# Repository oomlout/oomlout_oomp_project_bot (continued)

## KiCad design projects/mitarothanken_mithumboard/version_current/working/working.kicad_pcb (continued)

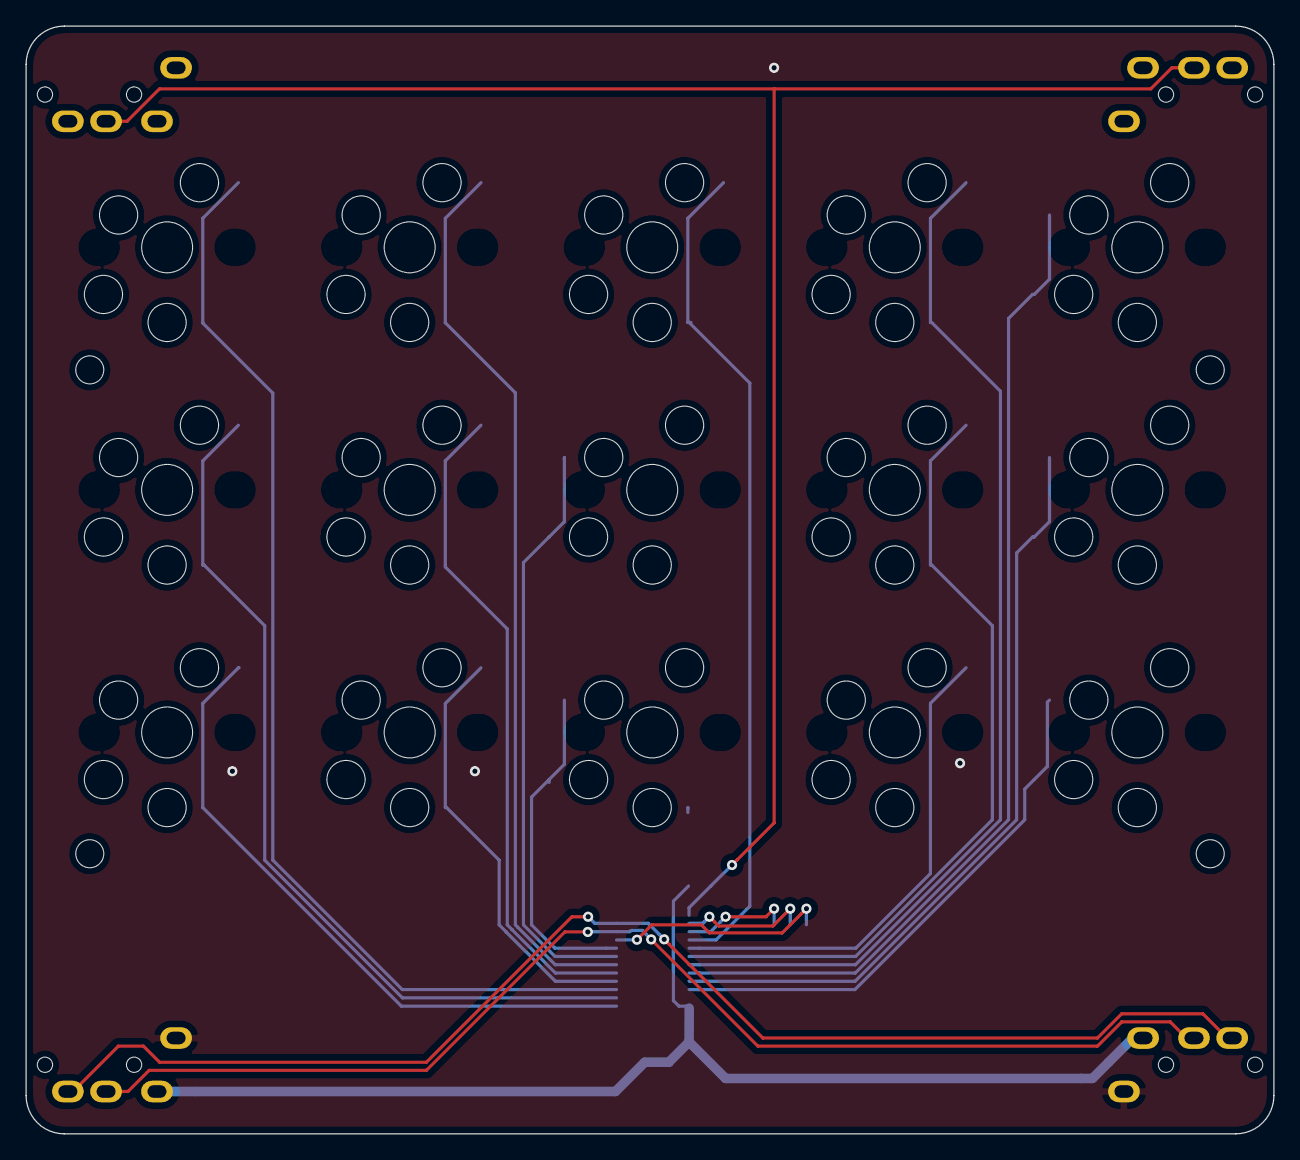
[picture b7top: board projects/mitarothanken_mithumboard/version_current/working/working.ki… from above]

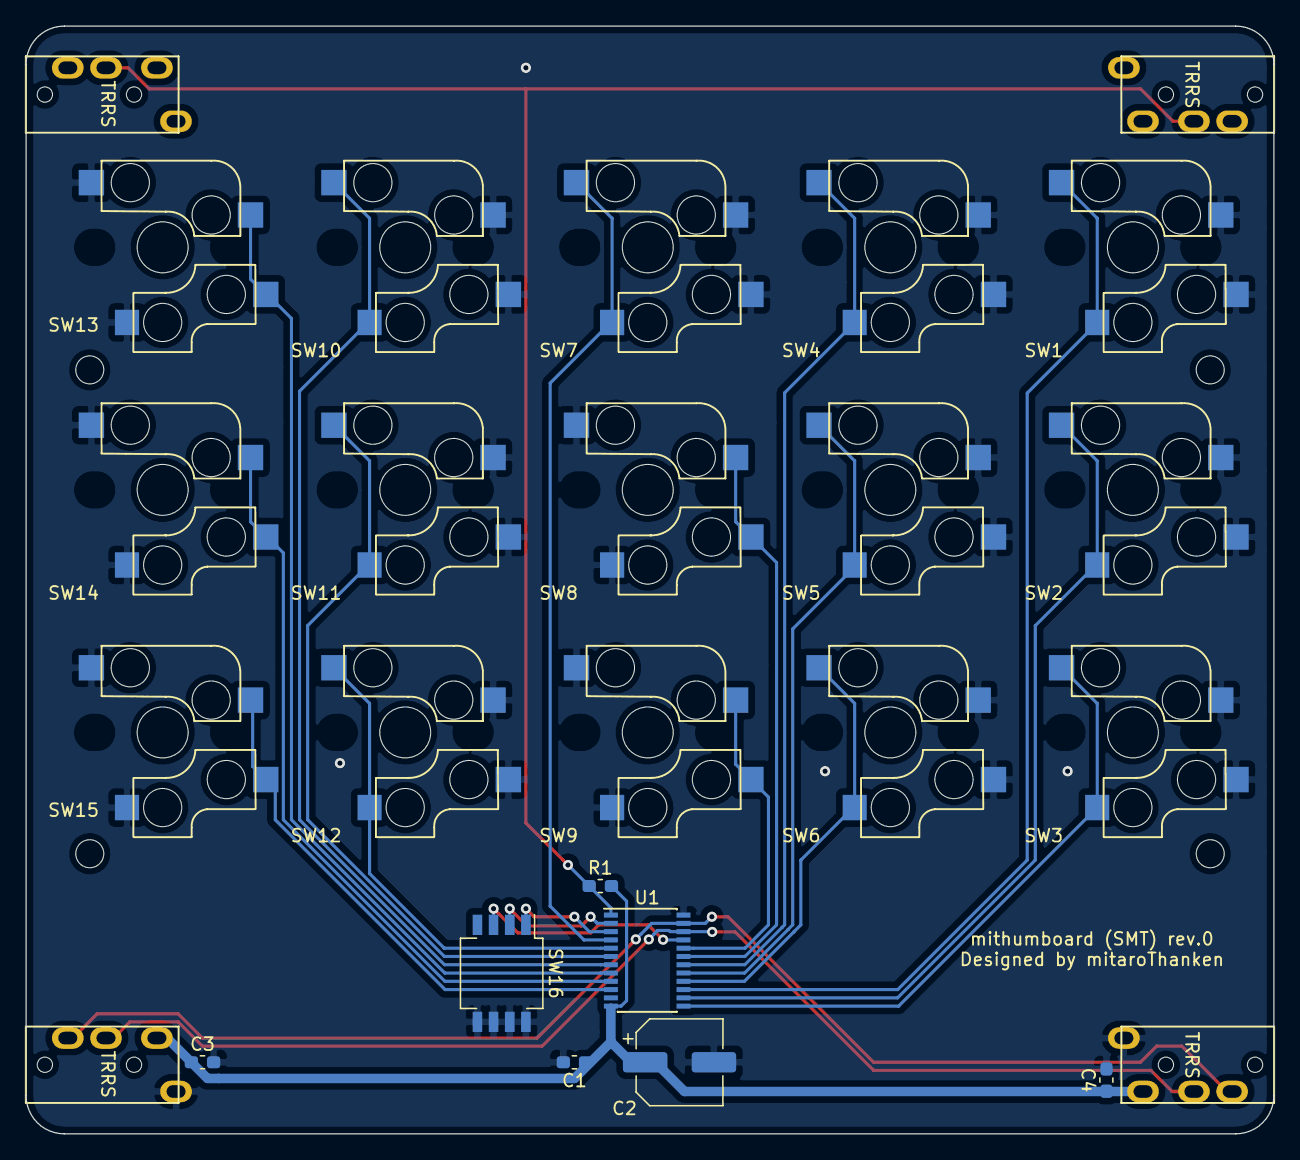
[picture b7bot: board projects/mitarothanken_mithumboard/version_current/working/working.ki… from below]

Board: 2 copper layers, 98.0 x 87.0 mm, 30 parts (15 on the bottom side), 23 nets.

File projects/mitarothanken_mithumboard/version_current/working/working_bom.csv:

"Id";"Designator";"Footprint";"Quantity";"Designation";"Supplier and ref";
1;"SW16";"SW_DIP_SPSTx04_Slide_Copal_CHS-04B_W7.62mm_P1.27mm";1;"SW_DIP_x04";;;
2;"R1";"R_0603_1608Metric_Pad1.05x0.95mm_HandSolder";1;"10k";;;
3;"C4,C3";"C_0603_1608Metric_Pad1.05x0.95mm_HandSolder";2;"1u";;;
4;"C2";"CP_Elec_6.3x5.4_Nichicon";1;"47u/16V";;;
5;"C1";"C_0603_1608Metric_Pad1.05x0.95mm_HandSolder";1;"0.1u";;;
6;"SW8,SW10,SW1,SW2,SW3,SW4,SW5,SW6,SW7,SW9,SW11,SW12,SW13,SW14,SW15";"CherryMX_Choc_Hotswap_1side";15;"SW_Push";;;
7;"U1";"TSSOP-24_4.4x7.8mm_P0.65mm";1;"TCA9555PWR";;;
8;"J1,J2,J3,J4";"MJ-4PP-9_1side";4;"MJ-4PP-9";;;
